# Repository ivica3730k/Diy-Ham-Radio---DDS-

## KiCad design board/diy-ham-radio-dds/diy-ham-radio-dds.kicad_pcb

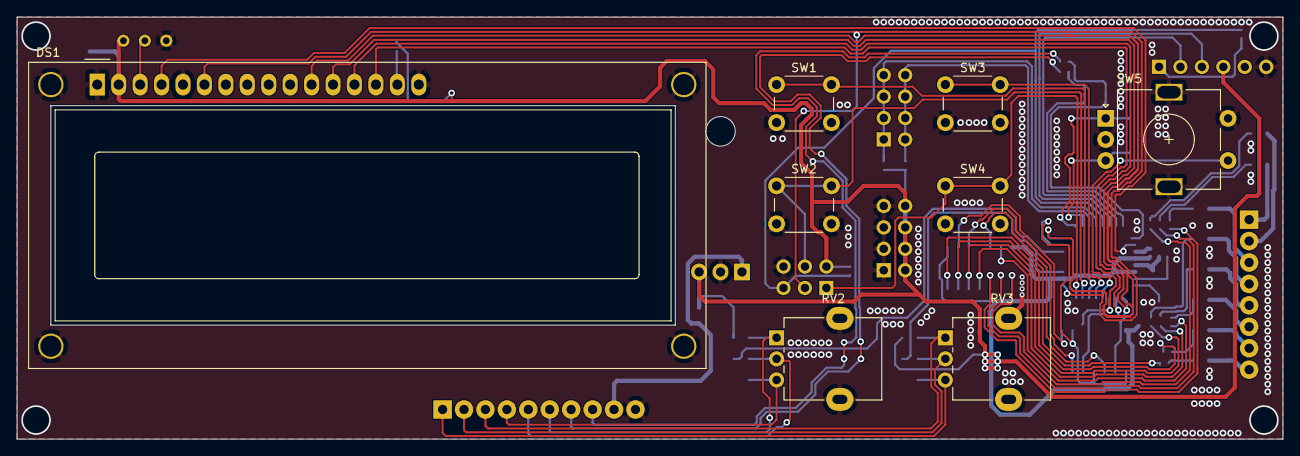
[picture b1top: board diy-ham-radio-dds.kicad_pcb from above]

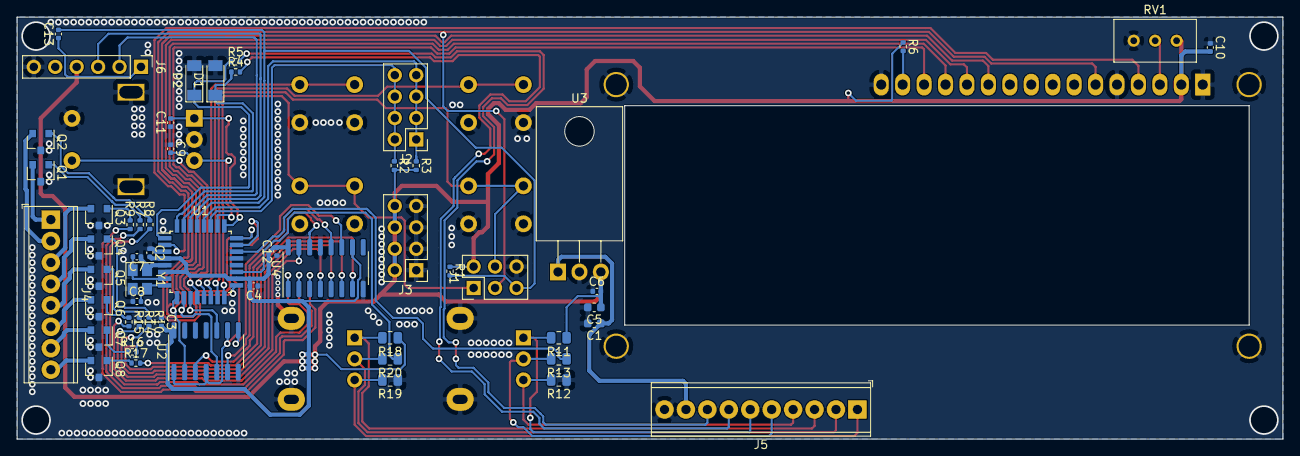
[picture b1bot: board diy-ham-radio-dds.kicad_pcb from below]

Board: 4 copper layers, 150.0 x 50.0 mm, 63 parts (55 on the bottom side), 66 nets.

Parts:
C1, C5: 22u; C_0603_1608Metric
C2, C3, C4, C6, C9, C10, C11, C12, C13: 100n; C_0402_1005Metric
C7, C8: 18p; C_0402_1005Metric
D1, D2: 4V7; D_MiniMELF
DS1: WC1602A
J1: ICSP; PinHeader_2x03_P2.54mm_Vertical
J2: I2C; PinHeader_2x04_P2.54mm_Vertical
J3: VCC; PinHeader_2x04_P2.54mm_Vertical
J4: NPN OUT; TerminalBlock_Phoenix_MPT-0,5-8-2.54_1x08_P2.54mm_Horizontal
J5: TerminalBlock_Phoenix_MPT-0,5-10-2.54_1x10_P2.54mm_Horizont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
J6: UART_PROG; PinHeader_1x06_P2.54mm_Vertical
Q1, Q2, Q3, Q4, Q5, Q6, Q7, Q8: S0805; SOT-23
R1: 10k; R_0402_1005Metric
R2, R3, R7, R8, R9, R10, R14, R15, R16, R17: 1k; R_0402_1005Metric
R4, R5: 100R; R_0402_1005Metric
R6: 220R 1/8W; R_0402_1005Metric
R11, R12, R13, R18, R19, R20: 0R; R_0805_2012Metric
RV1: 10k; Potentiometer_Bourns_3296W_Vertical
RV2, RV3: 10k; Potentiometer_Alpha_RD901F-40-00D_Single_Vertical
SW1, SW2, SW3, SW4: SW_Push; SW_PUSH_6mm
SW5: Rotary_Encoder_Switch; RotaryEncoder_Alps_EC11E-Switch_Vertical_H20mm
U1: ATmega328-AU; TQFP-32_7x7mm_P0.8mm
U2: 74LS08; SOIC-14_3.9x8.7mm_P1.27mm
U3: L7805; TO-220-3_Horizontal_TabDown
U4: 74HC595; SOIC-16_3.9x9.9mm_P1.27mm
Y1: 16MHz; Crystal_SMD_3225-4Pin_3.2x2.5mm

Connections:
ALARM: J5.8, R5.2
ALARM_IN: D2.1, R5.1, U1.1
DISP_D4: DS1.11, U1.24
DISP_D5\SHIFT_DATA: DS1.12, U1.9, U2.2
DISP_D6\SHIFT_LATCH: DS1.13, U1.10, U2.5
DISP_D7\SHIFT_CLOCK: DS1.14, U1.11, U2.10
DISP_EN: DS1.6, J1.3, U1.17
DISP_RS: DS1.4, U1.2
GND: C1.2, C2.1, C3.1, C4.1, C5.2, C6.1, C7.1, C8.1, C9.1, C10.1, C11.1, C12.1, D1.2, D2.2, DS1.1, DS1.5, DS1.16, J1.6, J3.1, J3.3, J3.5, J3.7, J5.10, J6.6, Q1.3, Q2.3, Q3.3, Q4.3, Q5.3, Q6.3, Q7.3, Q8.3, R12.1, R19.1, RV1.3, SW1.2, SW2.2, SW3.2, SW4.2, SW5.C, SW5.MP, SW5.S2, U1.3, U1.5, U1.21, U2.7, U3.2, U4.8, U4.13, Y1.2, Y1.4
unnamed: C7.2, U1.7, Y1.1
unnamed: C8.2, U1.8, Y1.3
unnamed: C13.1, J6.1
unnamed: DS1.3, RV1.2
unnamed: DS1.15, R6.2
unnamed: Q1.1, R7.1
unnamed: Q2.1, R8.1
unnamed: Q3.1, R9.1
unnamed: Q4.1, R10.1
unnamed: Q5.1, R14.1
unnamed: Q6.1, R15.1
unnamed: Q7.1, R16.1
unnamed: Q8.1, R17.1
POT1_A: J5.6, R11.2, RV2.1
POT1_B: J5.5, R13.2, RV2.2
POT1_C: J5.4, R12.2, RV2.3
POT2_A: J5.3, R18.2, RV3.1
POT2_B: J5.2, R20.2, RV3.2
POT2_C: J5.1, R19.2, RV3.3
POT_1: R13.1, U1.22
POT_2: R20.1, U1.19
PTT: J5.7, R4.2
PTT_IN: D1.1, R4.1, U1.32
Q1: J4.1, Q1.2
Q1_NPN: R7.2, U4.2
Q2: J4.2, Q2.2
Q2_NPN: R8.2, U4.1
Q3: J4.3, Q3.2
Q3_NPN: R9.2, U4.3
Q4: J4.4, Q4.2
Q4_NPN: R10.2, U4.5
Q5: J4.5, Q5.2
Q5_NPN: R14.2, U4.4
Q6: J4.6, Q6.2
Q6_NPN: R15.2, U4.15
Q7: J4.7, Q7.2
Q7_NPN: R16.2, U4.6
Q8: J4.8, Q8.2
Q8_NPN: R17.2, U4.7
ROT_A: C11.2, SW5.A, U1.25
ROT_B: C9.2, SW5.B, U1.26
RST: C13.2, J1.5, R1.2, U1.29
RX: J6.3, U1.30
SCL: J2.1, J2.3, J2.5, J2.7, R3.1, U1.28
SDA: J2.2, J2.4, J2.6, J2.8, R2.1, U1.27
SHIFT_CLOCK: U2.8, U4.11
SHIFT_DATA: U2.3, U4.14
SHIFT_ENABLE: U1.23, U2.1, U2.4, U2.9
SHIFT_LATCH: U2.6, U4.12
SW1: SW1.1, U1.14
SW2: J1.4, SW2.1, U1.15
SW3: SW3.1, U1.13
SW4: J1.1, SW4.1, U1.16
SW_ROT: SW5.S1, U1.12
TX: J6.2, U1.31
VCC: C2.2, C3.2, C4.2, C5.1, C6.2, C10.2, C12.2, DS1.2, J1.2, J3.2, J3.4, J3.6, J3.8, J6.4, R1.1, R2.2, R3.2, R6.1, R11.1, R18.1, RV1.1, U1.4, U1.6, U1.18, U2.14, U3.3, U4.10, U4.16
VIN: C1.1, J5.9, U3.1

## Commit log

2021-01-21 Created schematic
2021-01-21 Work in progress
2021-01-22 Routed display line signals
2021-01-22 Created minimal firmware from hardware specification
2021-01-22 Assigned footprints to the components
2021-01-22 Fixed wrong footprints
2021-01-22 Drawing in progress
2021-01-22 Updated footprints
2021-01-24 Working on firmware, updated .gitignore
2021-01-24 Working on firmware
2021-01-24 Changed NPN out channels in schematics
2021-01-26 Finalised board drawing
2021-01-26 DRC-Cleared for JLCPCB Production
    Used https://github.com/sethhillbrand/kicad_templates
2021-01-26 Added more tolerance to LCD cutout
